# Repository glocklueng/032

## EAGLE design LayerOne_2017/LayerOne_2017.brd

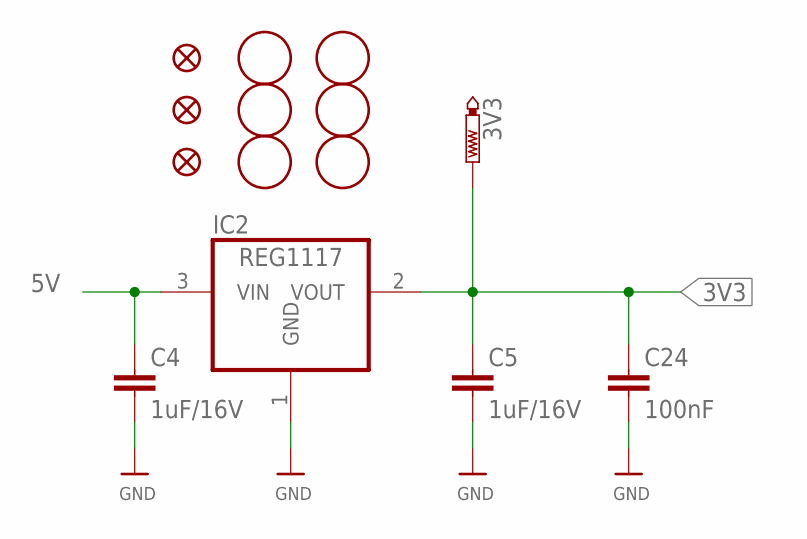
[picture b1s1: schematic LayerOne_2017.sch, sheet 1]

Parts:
3V3: PTR1PAD1-13; P1-13
C4, C5: 1uF/16V; 0805
C24: 100nF; 0805
FID1, FID2, FID3: FIDUCIALROUND; PASS-ROUND
IC2: REG1117; SOT223
U$3, U$4, U$5, U$7, U$8, U$9: FIDUCIAL; FIDUCIAL_1MM

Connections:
3V3: 3V3.TP, C5.1, C24.1, IC2.2 (VOUT); also elsewhere on the board
5V: C4.1, IC2.3 (VIN); also elsewhere on the board
GND: C4.2, C5.2, C24.2, IC2.1 (GND); also elsewhere on the board

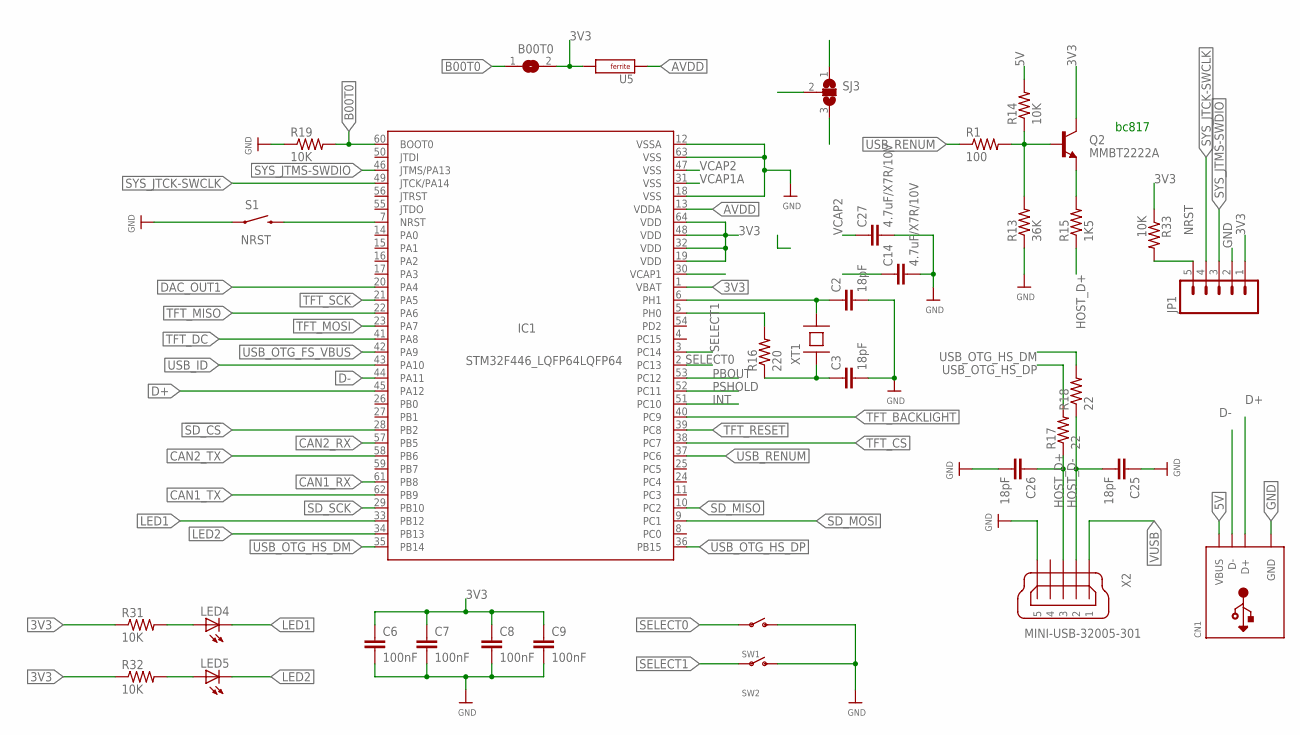
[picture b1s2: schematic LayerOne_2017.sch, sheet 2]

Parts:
B00T0: SJW
C2, C3, C25, C26: 18pF; 0805
C6, C7, C8, C9: 100nF; 0805
C14, C27: 4.7uF/X7R/10V; 0805
CN1: USB_TYPEAPTHFML; USB_HOST-PTH
IC1: STM32F446_LQFP64LQFP64; LQFP64
JP1: M05PTH; 1X05
LED4, LED5: LEDCHIP-LED0805; CHIP-LED0805
Q2: MMBT2222A; SOT23
R1: 100; 0805
R13: 36K; 0805
R14, R19, R31, R32, R33: 10K; 0805
R15: 1K5; 0805
R16: 220; 0805
R17, R18: 22; 0805; MPN RMCF0603JT10K0; DIGIKEY RMCF0603JT10K0CT-ND
S1: SPARKFUN_SWITCH-MOMENTARY-2SMD; SPARKFUN_TACTILE_SWITCH_SMD
SJ3: SJ2W; SJ_2
SW1, SW2: SWITCH_SPST; SPST_SMT_19192
U5: FERRITE0805; RLC_0805
X2: MINI-USB-32005-301; 32005-301
XT1: 8Mhz/16pF; XTAL-SMD-CITIZEN-CS10

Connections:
3V3: B00T0.2, C6.1, C7.1, C8.1, C9.1, IC1.1 (VBAT), IC1.19 (VDD), IC1.32 (VDD), IC1.48 (VDD), IC1.64 (VDD), JP1.1, Q2.3 (C), R31.1, R32.1, R33.1, U5.2 (B); also elsewhere on the board
5V: CN1.VBUS, R14.2; also elsewhere on the board
!SD_CS: IC1.28 (PB2); also elsewhere on the board
AVDD: IC1.13 (VDDA), U5.1 (A)
B00T0: B00T0.1, IC1.60 (BOOT0), R19.2
CAN1_RX: IC1.61 (PB8); also elsewhere on the board
CAN1_TX: IC1.62 (PB9); also elsewhere on the board
CAN2_RX: IC1.57 (PB5); also elsewhere on the board
CAN2_TX: IC1.58 (PB6); also elsewhere on the board
D+: CN1.D+, IC1.45 (PA12)
D-: CN1.D-, IC1.44 (PA11)
DAC_OUT1: IC1.20 (PA4); also elsewhere on the board
GND: C2.2, C3.2, C6.2, C7.2, C8.2, C9.2, C14.2, C25.1, C26.2, C27.2, CN1.GND, IC1.12 (VSSA), IC1.18 (VSS), IC1.63 (VSS), JP1.2, R13.1, R19.1, S1.1, SW1.C (S), SW2.C (S), X2.5; also elsewhere on the board
HOST_D+: C26.1, R15.1, R17.1, X2.3
HOST_D-: C25.2, R18.1, X2.2
INT: IC1.51 (PC10); also elsewhere on the board
LED1: IC1.33 (PB12), LED4.C
LED2: IC1.34 (PB13), LED5.C
unnamed: Q2.1 (B), R1.2, R13.2, R14.1
unnamed: Q2.2 (E), R15.2
unnamed: C2.1, IC1.6 (PH1), XT1.B
unnamed: C3.1, R16.1, XT1.A
unnamed: IC1.5 (PH0), R16.2
unnamed: LED4.A, R31.2
unnamed: LED5.A, R32.2
NRST: IC1.7 (NRST), JP1.5, R33.2, S1.3 (2); also elsewhere on the board
PBOUT: IC1.53 (PC12); also elsewhere on the board
PSHOLD: IC1.52 (PC11); also elsewhere on the board
SD_MISO: IC1.10 (PC2); also elsewhere on the board
SD_MOSI: IC1.9 (PC1); also elsewhere on the board
SD_SCK: IC1.29 (PB10); also elsewhere on the board
SELECT0: IC1.2 (PC13), SW1.B
SELECT1: IC1.3 (PC14), SW2.B
SYS_JTCK-SWCLK: IC1.49 (JTCK/PA14), JP1.4
SYS_JTMS-SWDIO: IC1.46 (JTMS/PA13), JP1.3
TFT_BACKLIGHT: IC1.40 (PC9); also elsewhere on the board
TFT_CS: IC1.38 (PC7); also elsewhere on the board
TFT_DC: IC1.41 (PA8); also elsewhere on the board
TFT_MISO: IC1.22 (PA6); also elsewhere on the board
TFT_MOSI: IC1.23 (PA7); also elsewhere on the board
TFT_RESET: IC1.39 (PC8); also elsewhere on the board
TFT_SCK: IC1.21 (PA5); also elsewhere on the board
USB_ID: IC1.43 (PA10)
USB_OTG_FS_VBUS: IC1.42 (PA9)
USB_OTG_HS_DM: IC1.35 (PB14), R18.2
USB_OTG_HS_DP: IC1.36 (PB15), R17.2
USB_RENUM: IC1.37 (PC6), R1.1
VCAP1: IC1.30 (VCAP1), SJ3.1
VCAP1A: IC1.31 (VSS), SJ3.3
VCAP1C: C14.1, SJ3.2
VCAP2: C27.1, IC1.47 (VSS)
VUSB: X2.1; also elsewhere on the board

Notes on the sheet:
bc817

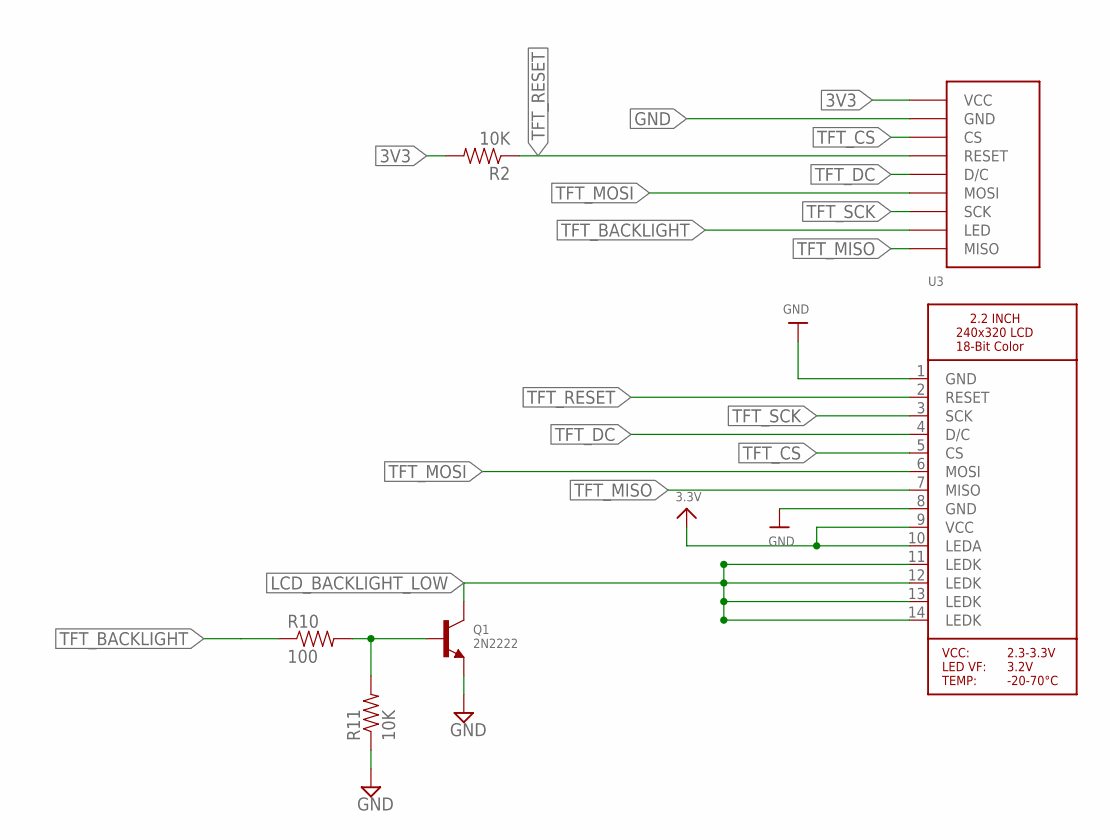
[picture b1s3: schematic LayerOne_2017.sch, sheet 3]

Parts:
J1: SPI_TFT_DISPLAY; SPI_DISPLAY
Q1: 2N2222; SOT23-WIDE
R2: 10K; 0805; MPN RMCF0603JT10K0; DIGIKEY RMCF0603JT10K0CT-ND
R10: 100; 0805
R11: 10K; 0805
U3: MICROBUILDER_DISP_LCD_TM022HDH26; MICROBUILDER_TM022HDH26_2.2IN_LCD

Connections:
3V3: J1.VCC, R2.2, U3.9 (VCC), U3.10 (LEDA); also elsewhere on the board
GND: J1.GND, Q1.2 (E), R11.1, U3.1 (GND), U3.8 (GND); also elsewhere on the board
LCD_BACKLIGHT_LOW: Q1.3 (C), U3.11 (LEDK), U3.12 (LEDK), U3.13 (LEDK), U3.14 (LEDK)
unnamed: Q1.1 (B), R10.2, R11.2
TFT_BACKLIGHT: J1.LED, R10.1; also elsewhere on the board
TFT_CS: J1.CS, U3.5 (CS); also elsewhere on the board
TFT_DC: J1.D/C, U3.4 (D/C); also elsewhere on the board
TFT_MISO: J1.MISO, U3.7 (MISO); also elsewhere on the board
TFT_MOSI: J1.MOSI, U3.6 (MOSI); also elsewhere on the board
TFT_RESET: J1.RESET, R2.1, U3.2 (RESET); also elsewhere on the board
TFT_SCK: J1.SCK, U3.3 (SCK); also elsewhere on the board

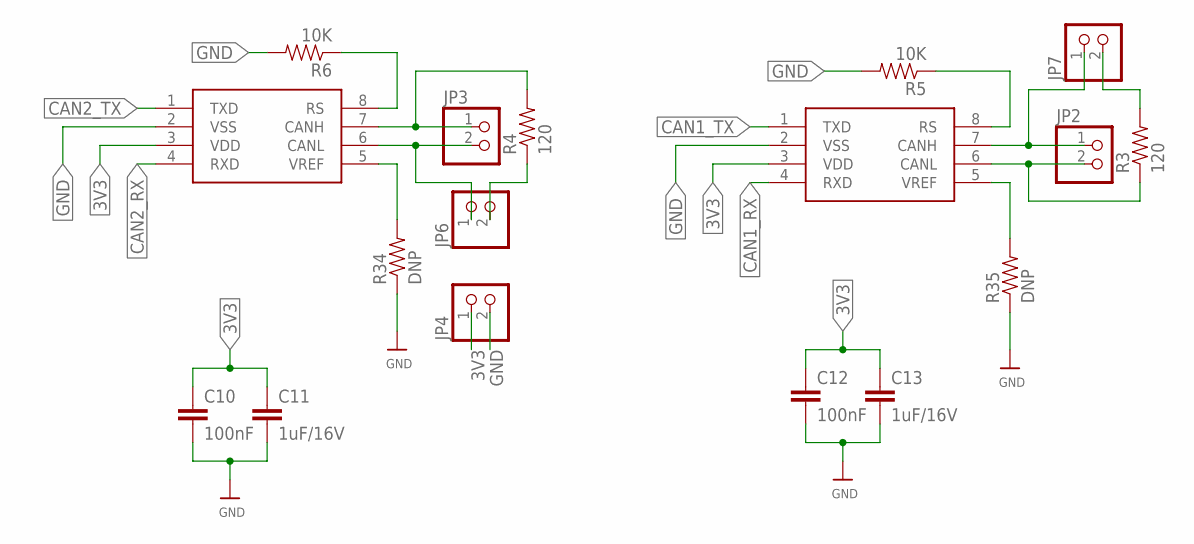
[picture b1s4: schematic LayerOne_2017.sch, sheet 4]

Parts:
C10, C12: 100nF; 0805
C11, C13: 1uF/16V; 0805
JP2, JP3, JP4, JP6, JP7: HEADER-1X2; 1X02_OVAL
R3, R4: 120; 0805; MPN RMCF0603JT10K0; DIGIKEY RMCF0603JT10K0CT-ND
R5, R6: 10K; 0805; MPN RMCF0603JT10K0; DIGIKEY RMCF0603JT10K0CT-ND
R34, R35: DNP; 0805; MPN RMCF0603JT10K0; DIGIKEY RMCF0603JT10K0CT-ND
U1, U2: SN65HVD235DR; SO08

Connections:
3V3: C10.1, C11.1, C12.1, C13.1, JP4.1, U1.3 (VDD), U2.3 (VDD); also elsewhere on the board
CAN1_RX: U2.4 (RXD); also elsewhere on the board
CAN1_TX: U2.1 (TXD); also elsewhere on the board
CAN2_RX: U1.4 (RXD); also elsewhere on the board
CAN2_TX: U1.1 (TXD); also elsewhere on the board
CANH1: JP2.1, JP7.1, U2.7 (CANH)
CANH2: JP3.1, R4.2, U1.7 (CANH)
CANL1: JP2.2, R3.1, U2.6 (CANL)
CANL2: JP3.2, JP6.1, U1.6 (CANL)
GND: C10.2, C11.2, C12.2, C13.2, JP4.2, R5.2, R6.2, R34.1, R35.1, U1.2 (VSS), U2.2 (VSS); also elsewhere on the board
unnamed: JP7.2, R3.2
unnamed: JP6.2, R4.1
unnamed: R34.2, U1.5 (VREF)
unnamed: R35.2, U2.5 (VREF)
SLOPE1: R5.1, U2.8 (RS)
SLOPE2: R6.1, U1.8 (RS)

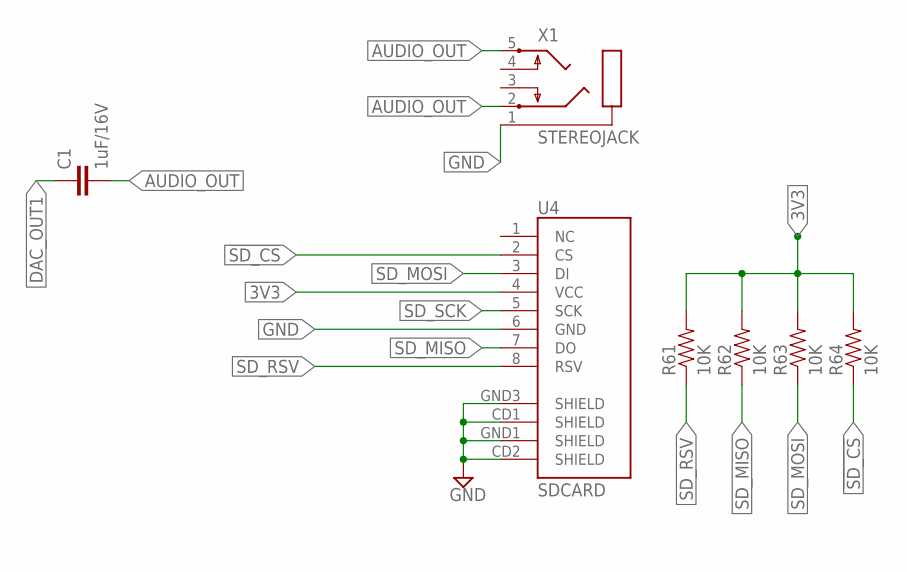
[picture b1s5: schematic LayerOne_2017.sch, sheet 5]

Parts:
C1: 1uF/16V; 0805
R61, R62, R63, R64: 10K; 0805; MPN RMCF0603JT10K0; DIGIKEY RMCF0603JT10K0CT-ND
U4: SDCARD; MICRO-SD-SOCKET-PP; PARTNO *
X1: STEREOJACK; STX3100

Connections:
3V3: R61.2, R62.2, R63.2, R64.2, U4.4 (VCC); also elsewhere on the board
!SD_CS: R64.1, U4.2 (CS); also elsewhere on the board
AUDIO_OUT: C1.2, X1.2, X1.5
DAC_OUT1: C1.1; also elsewhere on the board
GND: U4.6 (GND), U4.CD1 (SHIELD), U4.CD2 (SHIELD), U4.GND1 (SHIELD), U4.GND3 (SHIELD), X1.1; also elsewhere on the board
SD_MISO: R62.1, U4.7 (DO); also elsewhere on the board
SD_MOSI: R63.1, U4.3 (DI); also elsewhere on the board
SD_RSV: R61.1, U4.8 (RSV)
SD_SCK: U4.5 (SCK); also elsewhere on the board

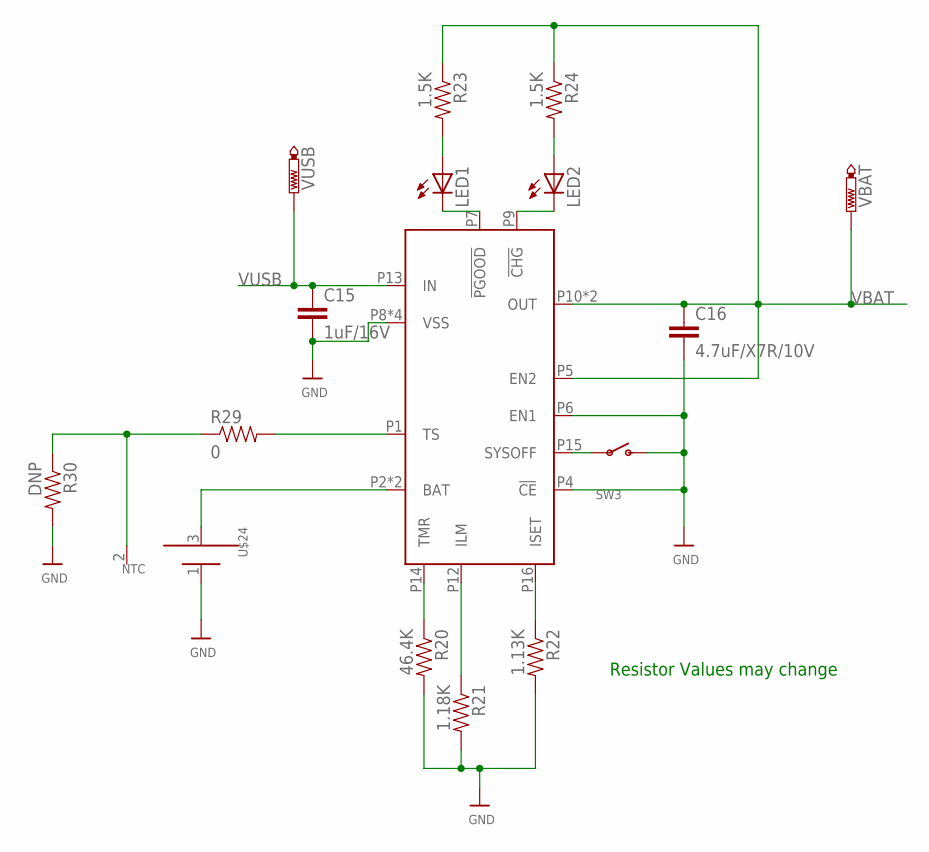
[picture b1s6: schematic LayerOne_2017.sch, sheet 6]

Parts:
C15: 1uF/16V; 0805
C16: 4.7uF/X7R/10V; 0805
LED1, LED2: LEDCHIPLED_0603; CHIPLED_0603
R20: 46.4K; 0805; MPN RMCF0603JT10K0; DIGIKEY RMCF0603JT10K0CT-ND
R21: 1.18K; 0805; MPN RMCF0603JT10K0; DIGIKEY RMCF0603JT10K0CT-ND
R22: 1.13K; 0805; MPN RMCF0603JT10K0; DIGIKEY RMCF0603JT10K0CT-ND
R23, R24: 1.5K; 0805; MPN RMCF0603JT10K0; DIGIKEY RMCF0603JT10K0CT-ND
R29: 0; 0805; MPN RMCF0603JT10K0; DIGIKEY RMCF0603JT10K0CT-ND
R30: DNP; 0805; MPN RMCF0603JT10K0; DIGIKEY RMCF0603JT10K0CT-ND
SW3: SWITCH_SPST; SPST_SMT_19192
U$23: TI-BQ2407XBQ24075; QFN16
U$24: BATT
VBAT: PTR1PAD1-13; P1-13
VUSB: PTR1PAD1-13; P1-13

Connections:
GND: C15.2, C16.2, R20.2, R21.2, R22.2, R30.2, SW3.C (S), U$23.P4 (!CE), U$23.P6 (EN1), U$23.P8 (VSS), U$23.XPAD@1 (VSS), U$23.XPAD@2 (VSS), U$23.XPAD@3 (VSS), U$24.1 (NEG); also elsewhere on the board
unnamed: R29.2, U$23.P1 (TS)
unnamed: U$23.P2 (BAT), U$23.P3 (BAT), U$24.3 (POS)
unnamed: LED1.C, U$23.P7 (!PGOOD)
unnamed: LED1.A, R23.2
unnamed: SW3.B, U$23.P15 (SYSOFF)
unnamed: R20.1, U$23.P14 (TMR)
unnamed: R21.1, U$23.P12 (ILM)
unnamed: R22.1, U$23.P16 (ISET)
unnamed: LED2.C, U$23.P9 (!CHG)
unnamed: LED2.A, R24.2
unnamed: R29.1, R30.1, U$24.2 (NTC)
VBAT: C16.1, R23.1, R24.1, U$23.P5 (EN2), U$23.P10 (OUT), U$23.P11 (OUT), VBAT.TP; also elsewhere on the board
VUSB: C15.1, U$23.P13 (IN), VUSB.TP; also elsewhere on the board

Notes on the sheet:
Resistor Values may change

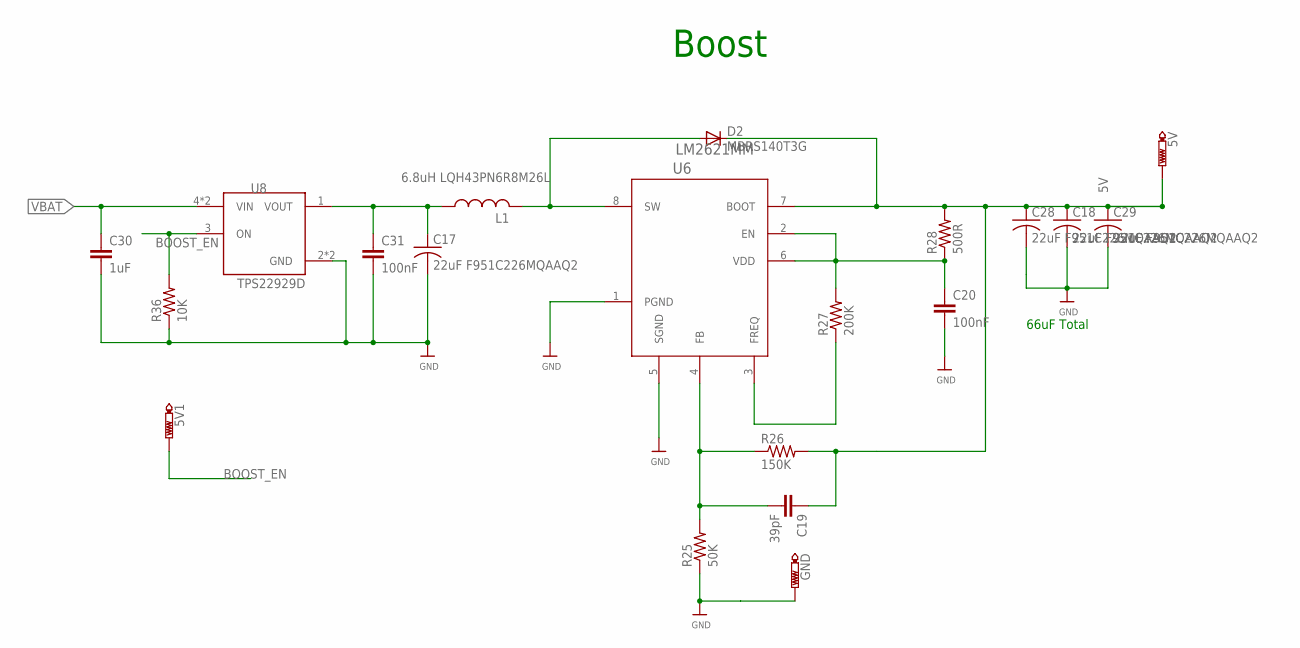
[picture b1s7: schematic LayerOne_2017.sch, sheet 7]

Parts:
5V: PTR1PAD1-13; P1-13
5V1: PTR1B1,27; B1,27
C17, C18, C28, C29: 22uF F951C226MQAAQ2; C1206
C19: 39pF; 0805
C20, C31: 100nF; 0805
C30: 1uF; 0805
D2: MBRS140T3G; SMB
GND: PTR1PAD1-13; P1-13
L1: 6.8uH LQH43PN6R8M26L; L1812
R25: 50K; 0805
R26: 150K; 0805
R27: 200K; 0805
R28: 500R; 0805
R36: 10K; 0805
U6: LM2621MM; SOP65P490X110-8N
U8: TPS22929D; SOT95P280X145-6N

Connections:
5V: 5V.TP, C18.1, C19.1, C28.1, C29.1, D2.C, R26.2, R28.2, U6.7 (BOOT); also elsewhere on the board
BOOST_EN: 5V1.TP, R36.2, U8.3 (ON); also elsewhere on the board
FB: C19.2, R25.2, R26.1, U6.4 (FB)
FREQ: R27.1, U6.3 (FREQ)
GND: C17.2, C18.2, C20.2, C28.2, C29.2, C30.2, C31.2, GND.TP, R25.1, R36.1, U6.1 (PGND), U6.5 (SGND), U8.2 (GND), U8.5 (GND); also elsewhere on the board
unnamed: C30.1, U8.4 (VIN), U8.6 (VIN)
SW: D2.A, L1.2, U6.8 (SW)
VBAT: C17.1, C31.1, L1.1, U8.1 (VOUT); also elsewhere on the board
VDD: C20.1, R27.2, R28.1, U6.2 (EN), U6.6 (VDD)

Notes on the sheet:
Boost
66uF Total

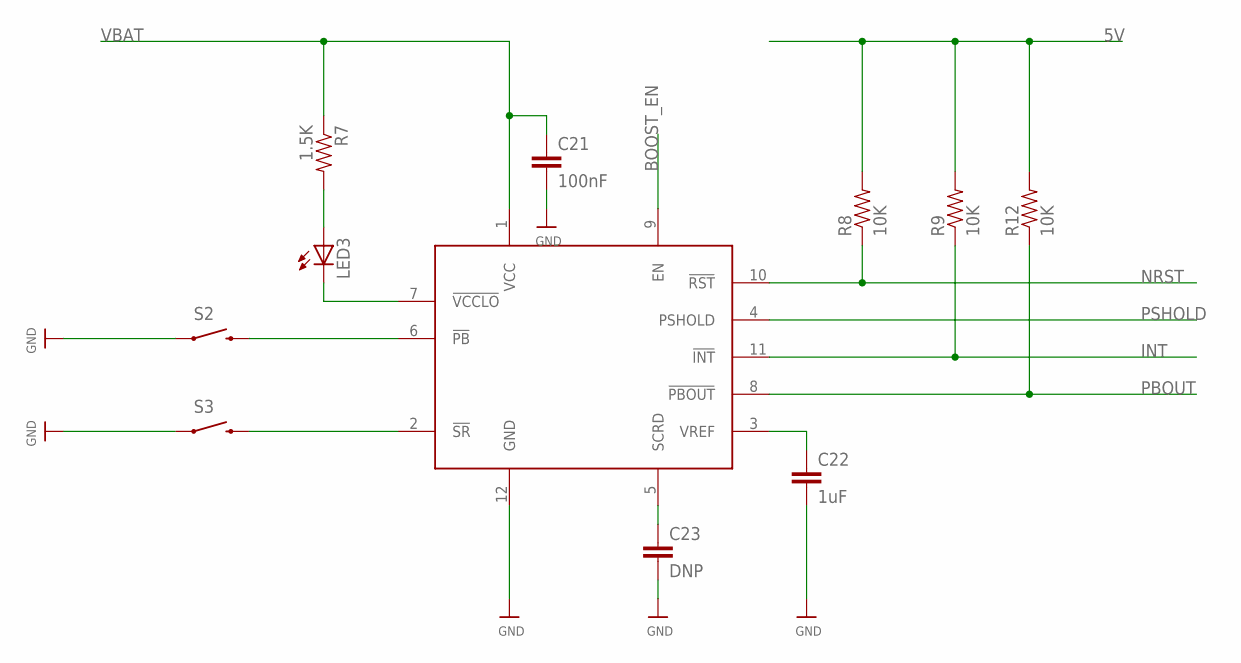
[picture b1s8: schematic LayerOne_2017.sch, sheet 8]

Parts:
C21: 100nF; 0805
C22: 1uF; 0805
C23: DNP; 0805
LED3: LEDCHIPLED_0603; CHIPLED_0603
R7: 1.5K; 0805; MPN RMCF0603JT10K0; DIGIKEY RMCF0603JT10K0CT-ND
R8, R9, R12: 10K; 0805
S2, S3: SPARKFUN_SWITCH-MOMENTARY-2SMD; SPARKFUN_TACTILE_SWITCH_SMD
U7: STM6600; TDFN12_STM

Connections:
5V: R8.2, R9.2, R12.2; also elsewhere on the board
BOOST_EN: U7.9 (EN); also elsewhere on the board
GND: C21.2, C22.2, C23.2, S2.1, S3.1, U7.12 (GND); also elsewhere on the board
INT: R9.1, U7.11 (!INT); also elsewhere on the board
unnamed: S2.3 (2), U7.6 (!PB)
unnamed: S3.3 (2), U7.2 (!SR)
unnamed: LED3.C, U7.7 (!VCCLO)
unnamed: LED3.A, R7.2
unnamed: C22.1, U7.3 (VREF)
unnamed: C23.1, U7.5 (SCRD)
NRST: R8.1, U7.10 (!RST); also elsewhere on the board
PBOUT: R12.1, U7.8 (!PBOUT); also elsewhere on the board
PSHOLD: U7.4 (PSHOLD); also elsewhere on the board
VBAT: C21.1, R7.1, U7.1 (VCC); also elsewhere on the board

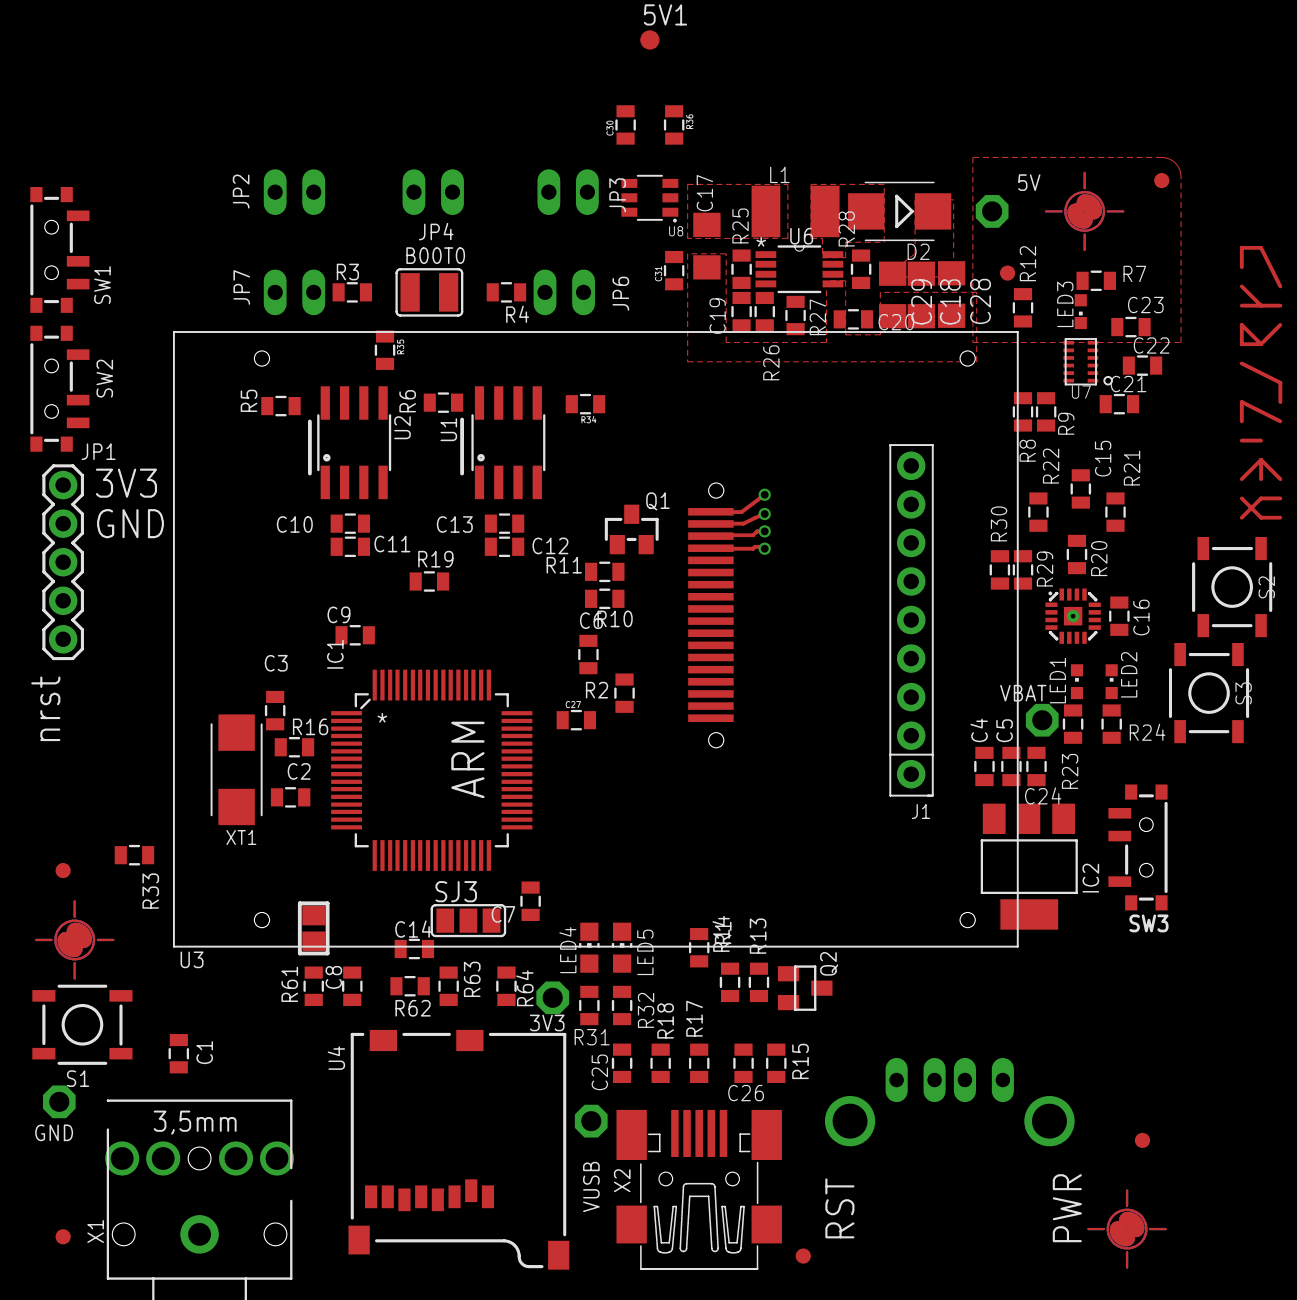
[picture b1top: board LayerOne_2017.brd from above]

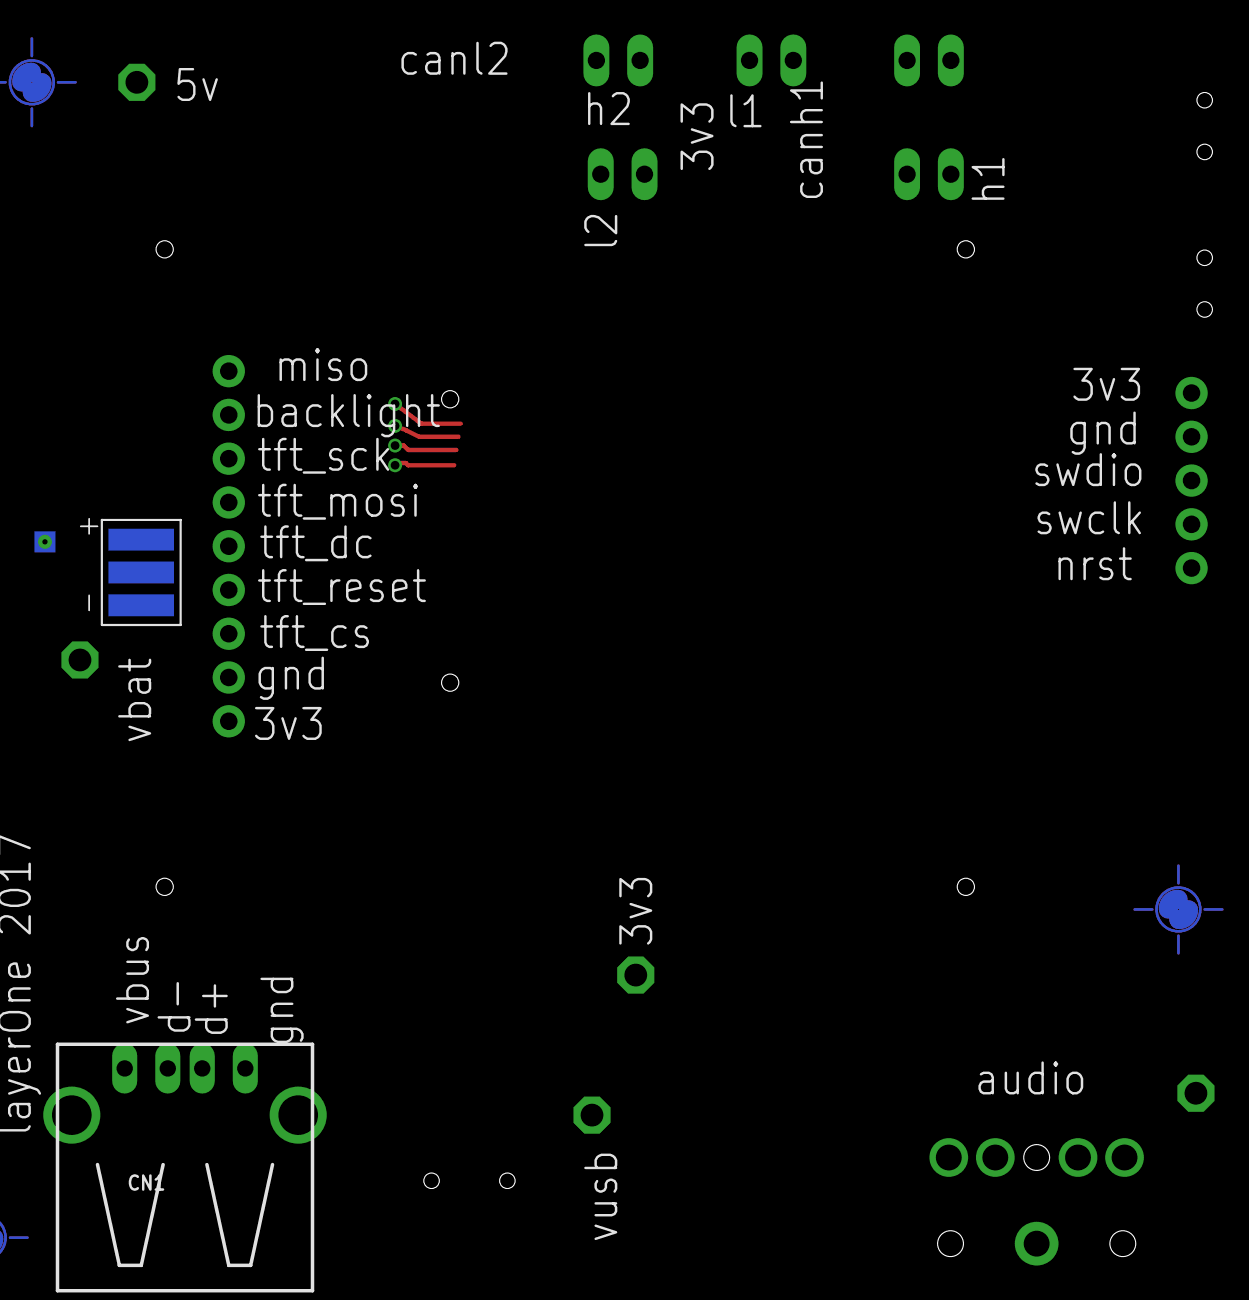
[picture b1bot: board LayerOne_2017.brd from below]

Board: 2 copper layers, 126 parts (2 on the bottom side), 88 nets.

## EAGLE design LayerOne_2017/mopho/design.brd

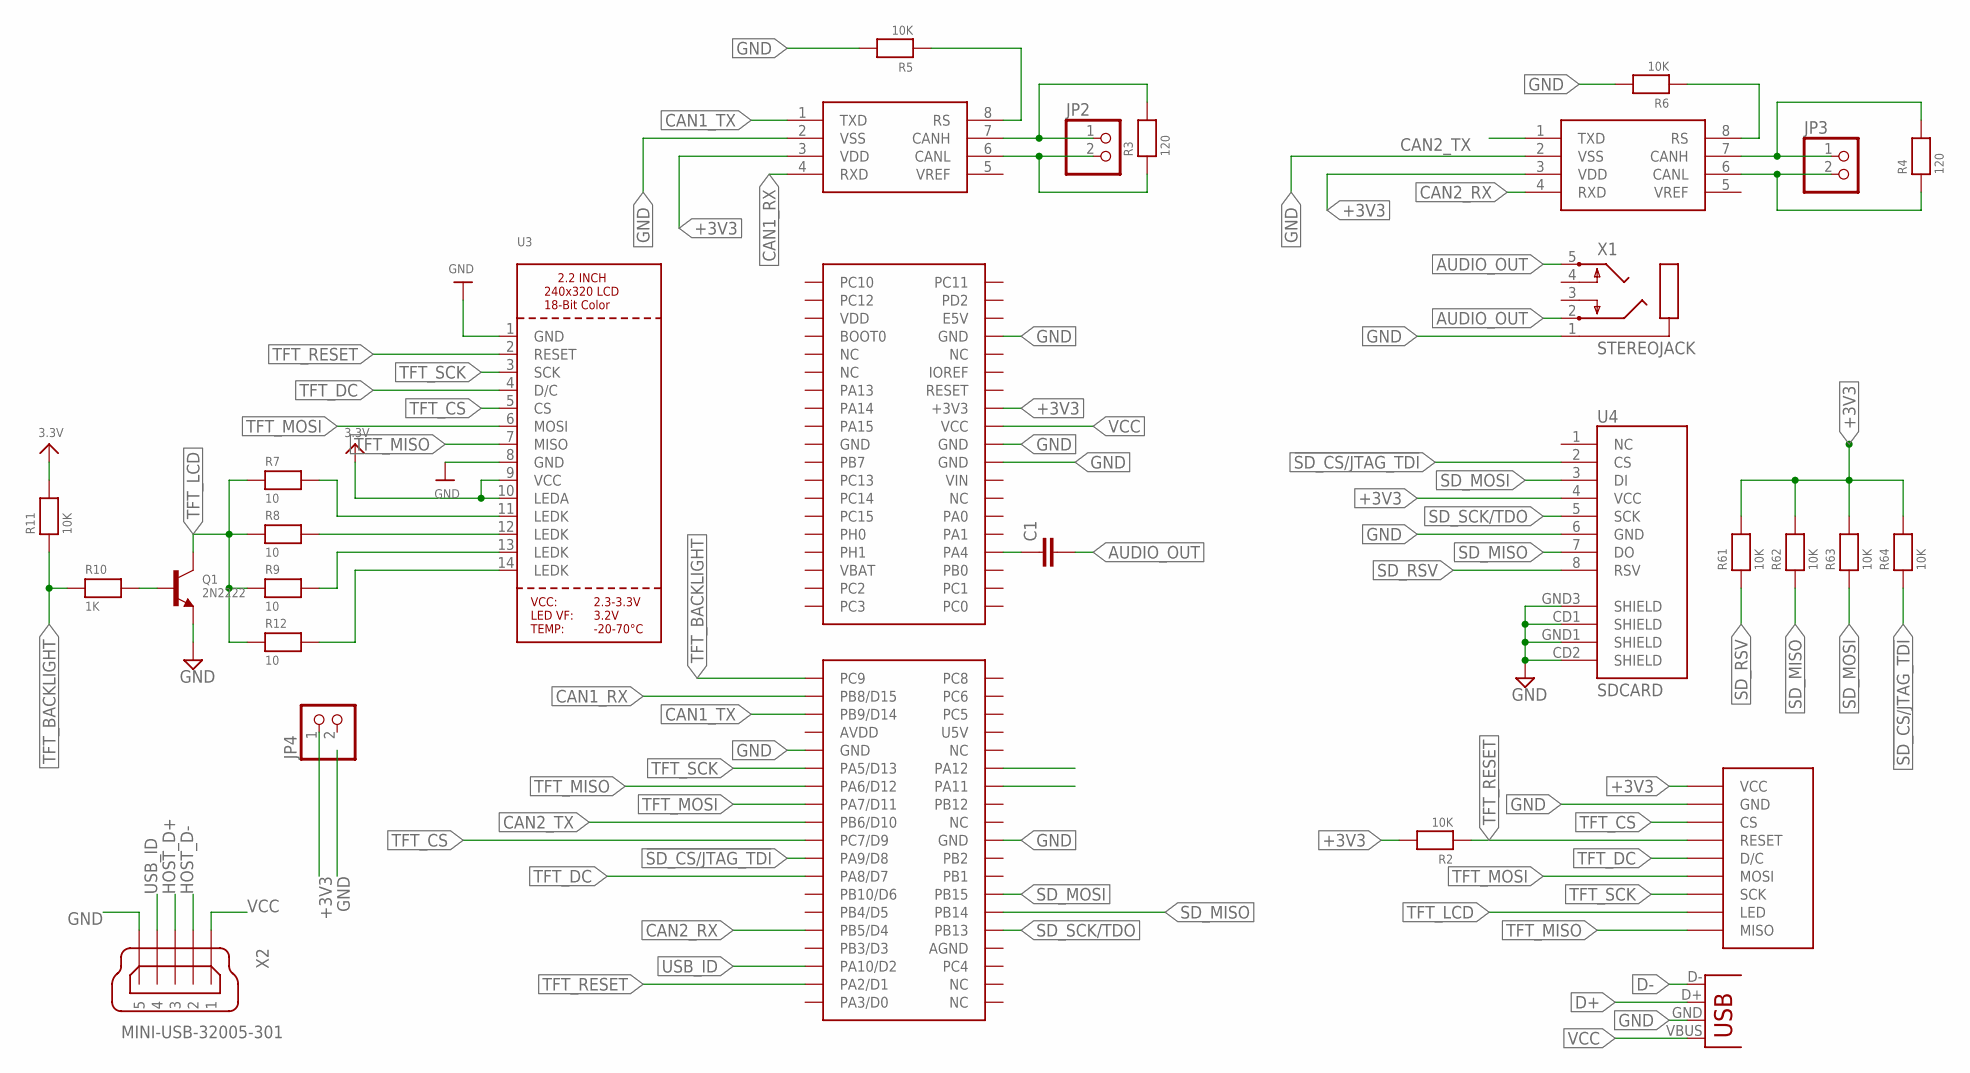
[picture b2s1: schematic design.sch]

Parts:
C1: CAP1206; 1206
J1: SPI_TFT_DISPLAY; SPI_DISPLAY
JP1: USB-A-H
JP2, JP3, JP4: HEADER-1X2; 1X02_OVAL
Q1: 2N2222; SOT23-WIDE
R2, R5, R6, R61, R62, R63, R64: 10K; _0805; MPN RMCF0603JT10K0; DIGIKEY RMCF0603JT10K0CT-ND
R3, R4: 120; _0805; MPN RMCF0603JT10K0; DIGIKEY RMCF0603JT10K0CT-ND
R7, R8, R9, R12: 10; _0805
R10: 1K; _0805
R11: 10K; _0805
U1, U2: SN65HVD235DR; SO08
U3: DISP_LCD_TM022HDH26; TM022HDH26_2.2IN_LCD
U4: SDCARD; MICRO-SD-SOCKET-PP; PARTNO *
U$1: MOPHOMOPHO_466RE; MOPHO
X1: STEREOJACK; STX3100
X2: MINI-USB-32005-301; 32005-301

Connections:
3.3V: R11.2
!SD_CS/JTAG_TDI: R64.1, U4.2 (CS), U$1.P$59 (PA9/D8)
+3V3: J1.VCC, JP4.1, R2.2, R61.2, R62.2, R63.2, R64.2, U1.3 (VDD), U2.3 (VDD), U3.9 (VCC), U3.10 (LEDA), U4.4 (VCC), U$1.P$16 (+3V3)
AUDIO_OUT: C1.2, X1.2, X1.5
AVDD: U$1.P$45 (AVDD)
CAN1_RX: U2.4 (RXD), U$1.P$41 (PB8/D15)
CAN1_TX: U2.1 (TXD), U$1.P$43 (PB9/D14)
CAN2_RX: U1.4 (RXD), U$1.P$67 (PB5/D4)
CAN2_TX: U1.1 (TXD), U$1.P$55 (PB6/D10)
CANH1: JP2.1, R3.2, U2.7 (CANH)
CANH2: JP3.1, R4.2, U1.7 (CANH)
CANL1: JP2.2, R3.1, U2.6 (CANL)
CANL2: JP3.2, R4.1, U1.6 (CANL)
D+: JP1.D+ (D-), U$1.P$50 (PA12)
D-: JP1.D- (D+), U$1.P$52 (PA11)
GND: J1.GND, JP1.GND (VBUS), Q1.2 (E), R5.2, R6.2, U1.2 (VSS), U2.2 (VSS), U3.1 (GND), U3.8 (GND), U4.6 (GND), U4.CD1 (SHIELD), U4.CD2 (SHIELD), U4.GND1 (SHIELD), U4.GND3 (SHIELD), U$1.P$8 (GND), U$1.P$20 (GND), U$1.P$22 (GND), U$1.P$47 (GND), U$1.P$58 (GND), X1.1, X2.5
HOST_D+: X2.3
HOST_D-: X2.2
unnamed: C1.1, U$1.P$32 (PA4)
unnamed: R6.1, U1.8 (RS)
unnamed: R5.1, U2.8 (RS)
unnamed: R7.2, U3.11 (LEDK)
unnamed: R8.2, U3.12 (LEDK)
unnamed: R9.2, U3.13 (LEDK)
unnamed: Q1.1 (B), R10.2
unnamed: R12.2, U3.14 (LEDK)
SD_MISO: R62.1, U4.7 (DO), U$1.P$66 (PB14)
SD_MOSI: R63.1, U4.3 (DI), U$1.P$64 (PB15)
SD_RSV: R61.1, U4.8 (RSV)
SD_SCK/TDO: U4.5 (SCK), U$1.P$68 (PB13)
TFT_BACKLIGHT: R10.1, R11.1, U$1.P$39 (PC9)
TFT_CS: J1.CS, U3.5 (CS), U$1.P$57 (PC7/D9)
TFT_DC: J1.D/C, U3.4 (D/C), U$1.P$61 (PA8/D7)
TFT_LCD: J1.LED, Q1.3 (C), R7.1, R8.1, R9.1, R12.1
TFT_MISO: J1.MISO, U3.7 (MISO), U$1.P$51 (PA6/D12)
TFT_MOSI: J1.MOSI, U3.6 (MOSI), U$1.P$53 (PA7/D11)
TFT_RESET: J1.RESET, R2.1, U3.2 (RESET), U$1.P$73 (PA2/D1)
TFT_SCK: J1.SCK, U3.3 (SCK), U$1.P$49 (PA5/D13)
USB_ID: U$1.P$71 (PA10/D2), X2.4
VBAT: U$1.P$33 (VBAT)
VCC: JP1.VBUS (GND), U$1.P$18 (VCC), X2.1
VDD: U$1.P$5 (VDD)
VIN: U$1.P$24 (VIN)

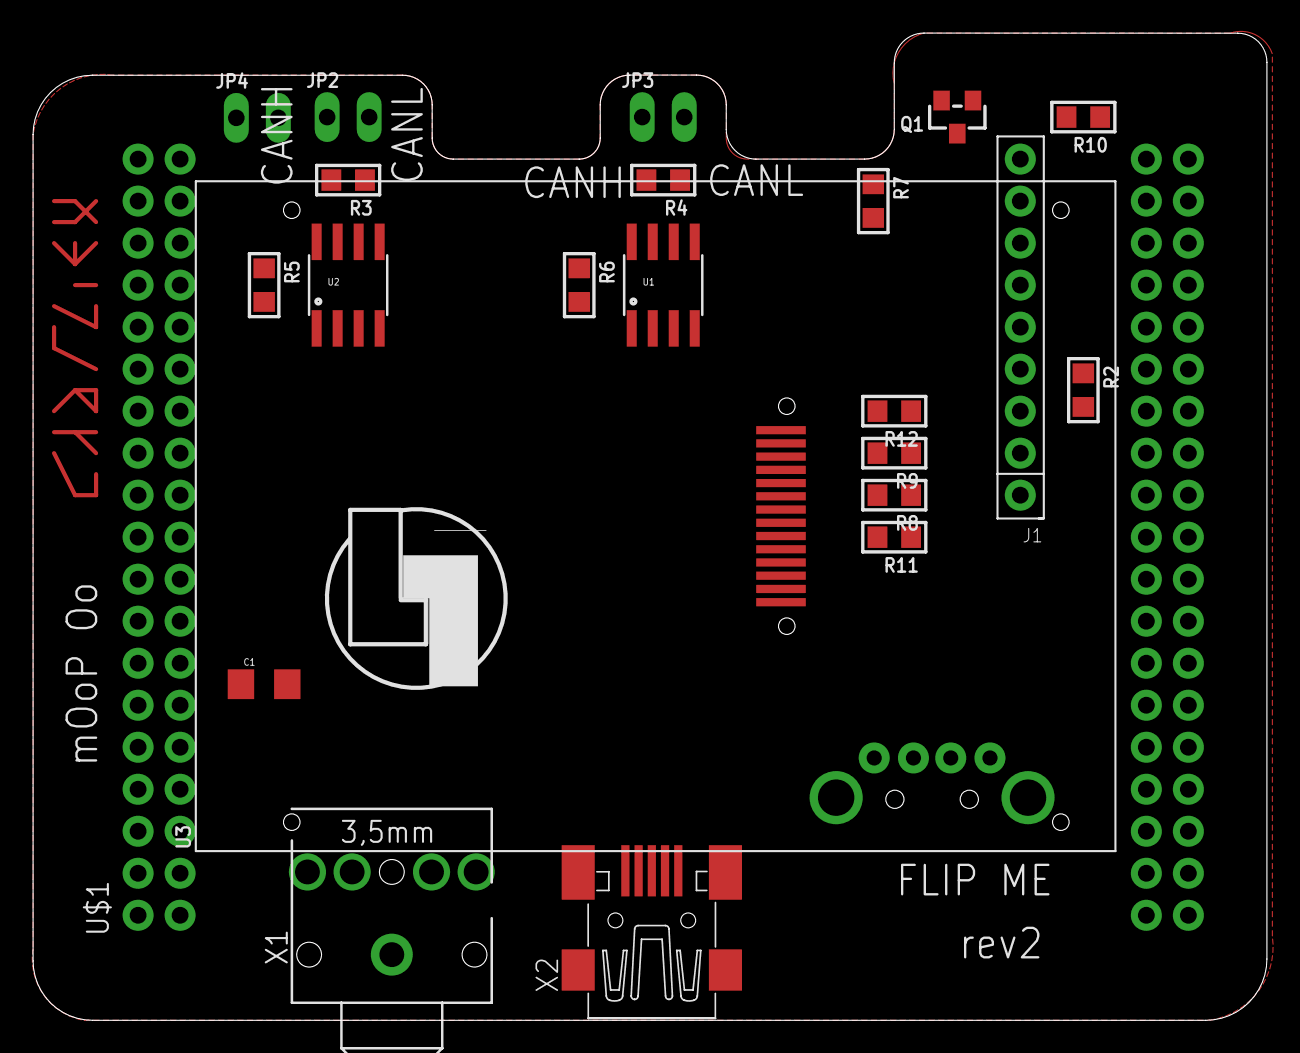
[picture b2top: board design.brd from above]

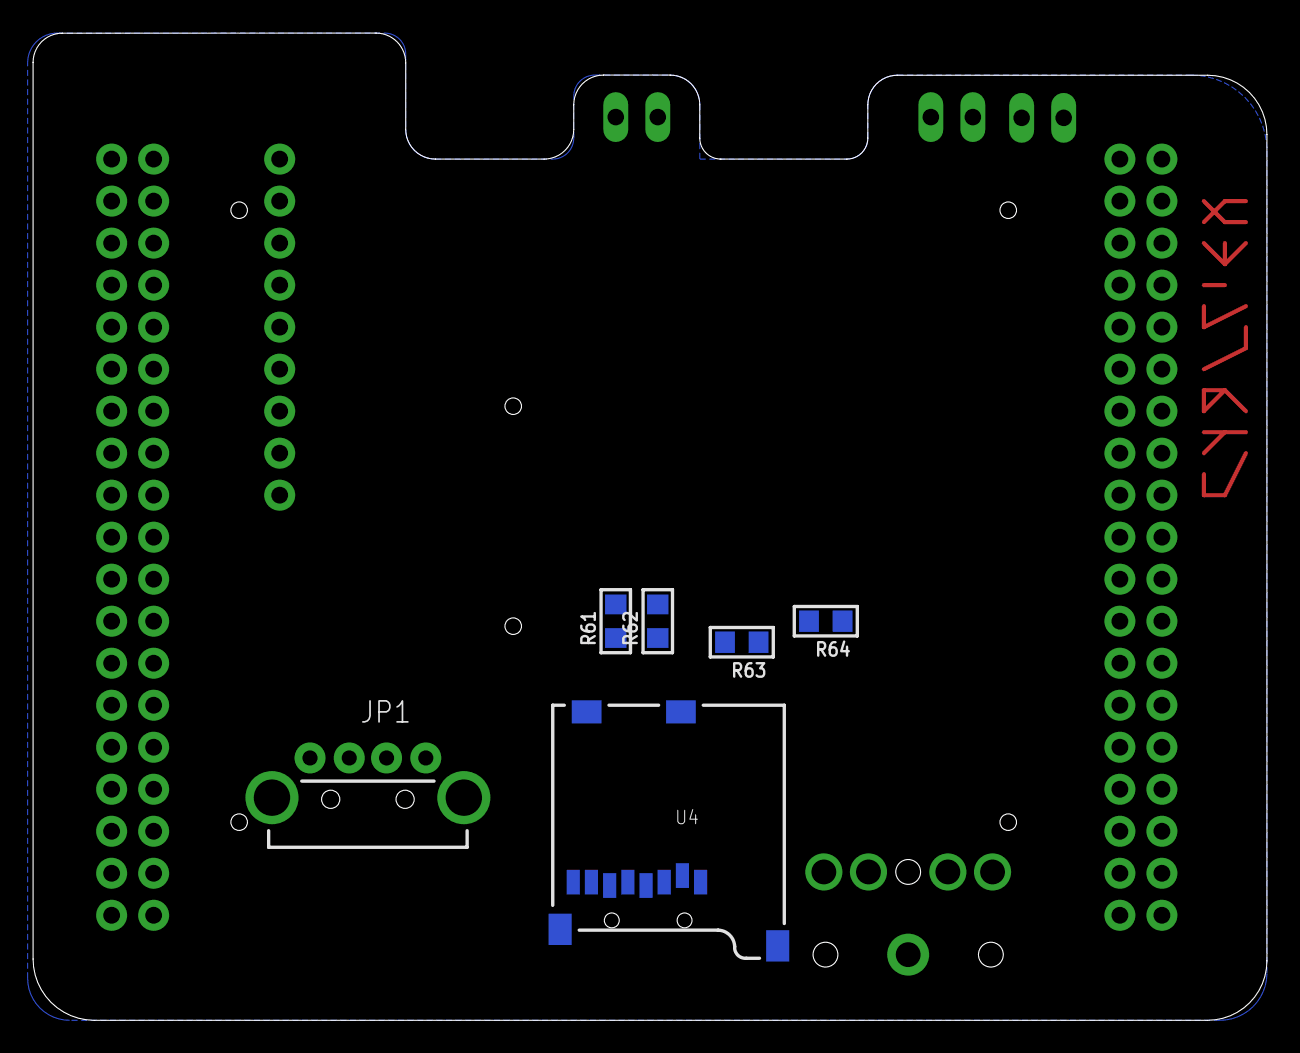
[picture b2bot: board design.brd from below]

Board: 2 copper layers, 74.6 x 59.7 mm, 29 parts (6 on the bottom side), 36 nets.

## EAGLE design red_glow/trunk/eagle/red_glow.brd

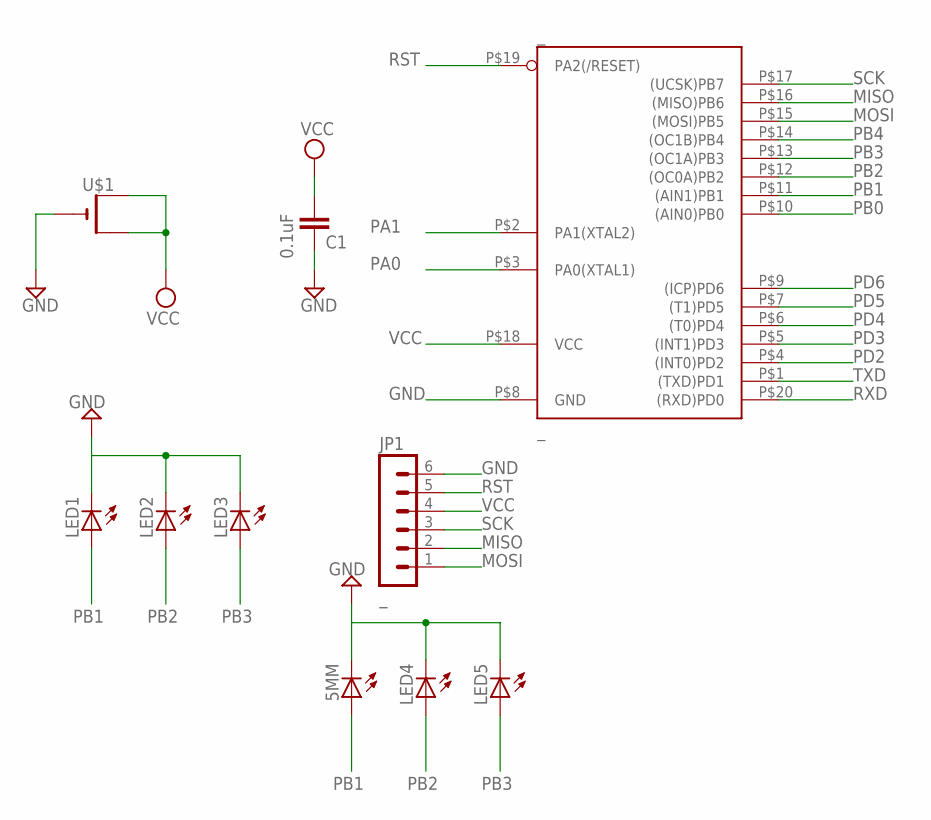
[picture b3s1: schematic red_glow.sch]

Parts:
5MM: LED5MM
C1: 0.1uF; 0805
JP1: _; MA06-1
LED1, LED2, LED3: LED1206; LED-1206
LED4, LED5: LED5MM
U$1: CR2032SMT; CR2032-SMD
_: _; MLF20

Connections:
GND: 5MM.K (C), C1.2, JP1.6, LED1.C, LED2.C, LED3.C, LED4.K (C), LED5.K (C), U$1.-, _.P$8 (GND)
MISO: JP1.2, _.P$16 ((MISO)PB6)
MOSI: JP1.1, _.P$15 ((MOSI)PB5)
PA0: _.P$3 (PA0(XTAL1))
PA1: _.P$2 (PA1(XTAL2))
PB0: _.P$10 ((AIN0)PB0)
PB1: 5MM.A, LED1.A, _.P$11 ((AIN1)PB1)
PB2: LED2.A, LED4.A, _.P$12 ((OC0A)PB2)
PB3: LED3.A, LED5.A, _.P$13 ((OC1A)PB3)
PB4: _.P$14 ((OC1B)PB4)
PD2: _.P$4 ((INT0)PD2)
PD3: _.P$5 ((INT1)PD3)
PD4: _.P$6 ((T0)PD4)
PD5: _.P$7 ((T1)PD5)
PD6: _.P$9 ((ICP)PD6)
RST: JP1.5, _.P$19 (PA2(/RESET))
RXD: _.P$20 ((RXD)PD0)
SCK: JP1.3, _.P$17 ((UCSK)PB7)
TXD: _.P$1 ((TXD)PD1)
VCC: C1.1, JP1.4, U$1.+$1 (+), U$1.+$2 (+1), _.P$18 (VCC)

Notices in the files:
LayerOne_2017/cube/STM32F4_64PIN/Src/main.c:
Copyright (c) 2016 STMicroelectronics International N.V.
All rights reserved.
(C) COPYRIGHT STMicroelectronics *****END OF FILE
parts and their libraries:
SparkFun-Resistors: Licensing: CC v3.0 Share-Alike You are welcome to use this library for commercial purposes.
microbuilder: This work is placed in the public domain, and may be freely used for commercial and non-commercial work with the following conditions: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
